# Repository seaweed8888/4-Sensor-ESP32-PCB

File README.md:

# 4-Sensor-ESP32-PCB
Thermister, Vibration Sensor, Light Sensor, Button connected to a esp32s3 to make a LED do stuff

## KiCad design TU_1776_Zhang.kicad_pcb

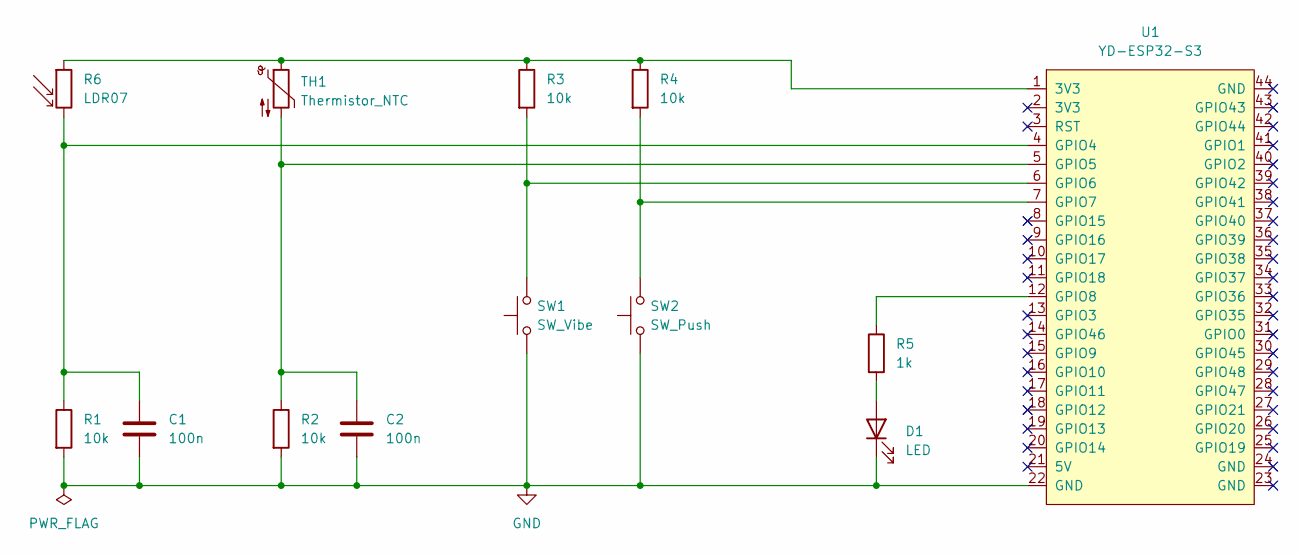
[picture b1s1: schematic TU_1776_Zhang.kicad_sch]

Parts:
C1, C2: 100n; C_Disc_D5.1mm_W3.2mm_P5.00mm
D1: LED; LED_D5.0mm
R1, R2, R3, R4: 10k; R_Axial_DIN0309_L9.0mm_D3.2mm_P12.70mm_Horizontal
R5: 1k; R_Axial_DIN0309_L9.0mm_D3.2mm_P12.70mm_Horizontal
R6: LDR07; R_LDR_5.1x4.3mm_P3.4mm_Vertical
SW1: SW_Vibe; CP_Radial_D5.0mm_P2.50mm
SW2: SW_Push; SW_PUSH_6mm_2pin
TH1: Thermistor_NTC; CP_Radial_D5.0mm_P2.50mm
U1: YD-ESP32-S3

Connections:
GND: C1.2, C2.2, D1.1 (K), R1.2, R2.2, SW1.1, SW2.1, U1.22 (GND)
unnamed: D1.2 (A), R5.2
unnamed: R3.1, R4.1, R6.1, TH1.1, U1.1 (3V3)
unnamed: C1.1, R1.1, R6.2, U1.4 (GPIO4)
unnamed: C2.1, R2.1, TH1.2, U1.5 (GPIO5)
unnamed: R3.2, SW1.2, U1.6 (GPIO6)
unnamed: R4.2, SW2.2, U1.7 (GPIO7)
unnamed: R5.1, U1.12 (GPIO8)

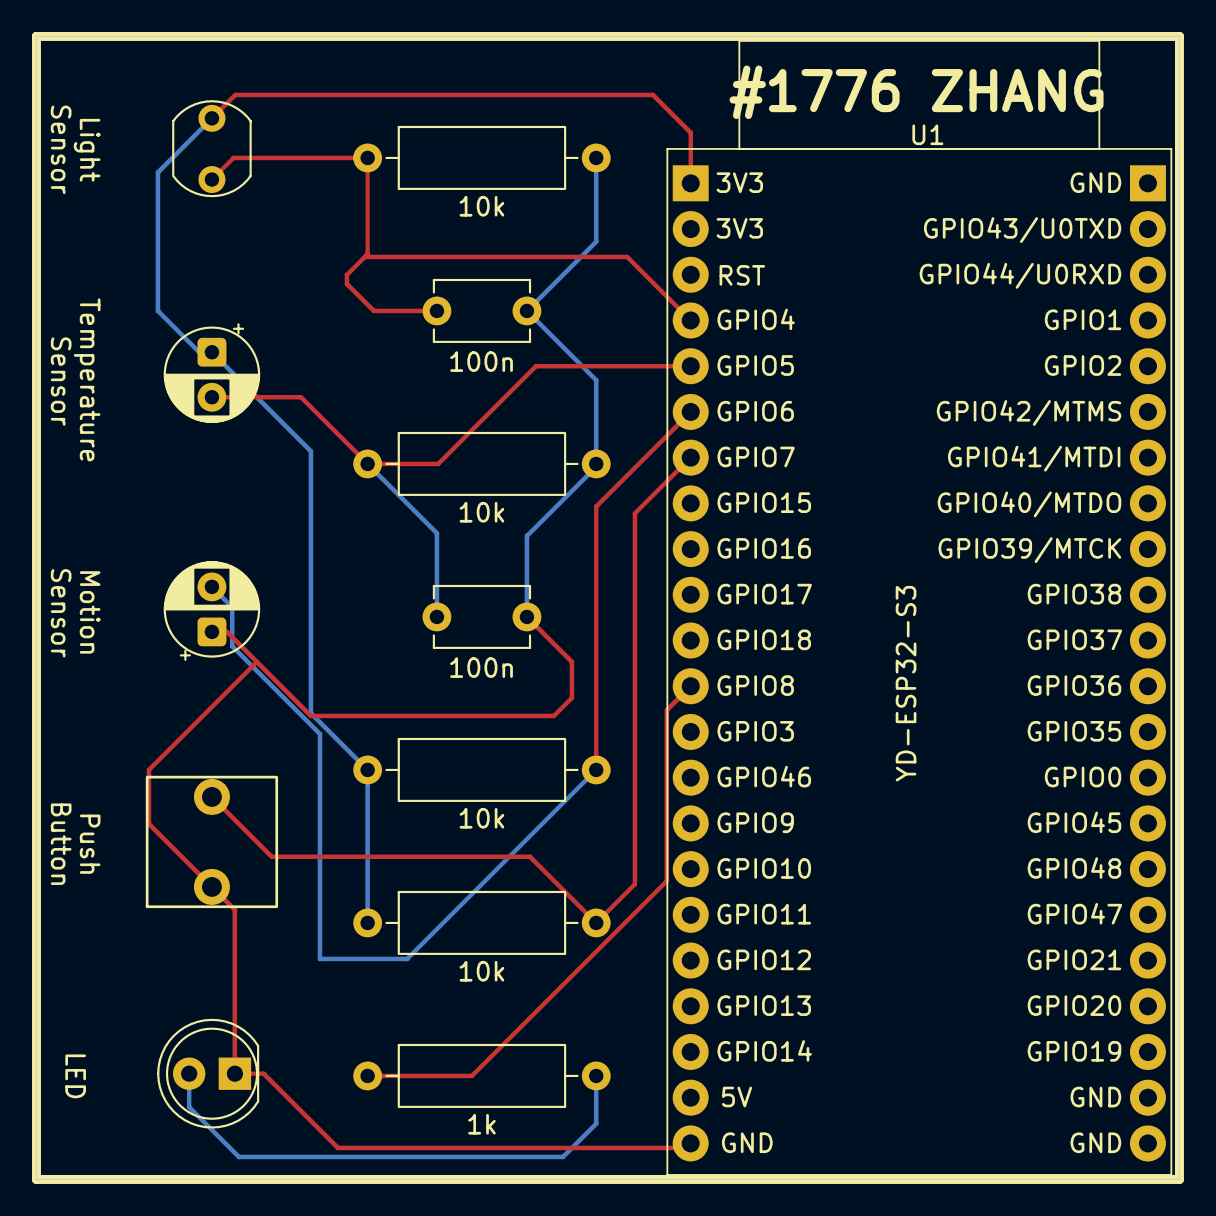
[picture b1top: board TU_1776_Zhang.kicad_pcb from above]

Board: 2 copper layers, 63.5 x 63.5 mm, 13 parts (0 on the bottom side), 8 nets.
